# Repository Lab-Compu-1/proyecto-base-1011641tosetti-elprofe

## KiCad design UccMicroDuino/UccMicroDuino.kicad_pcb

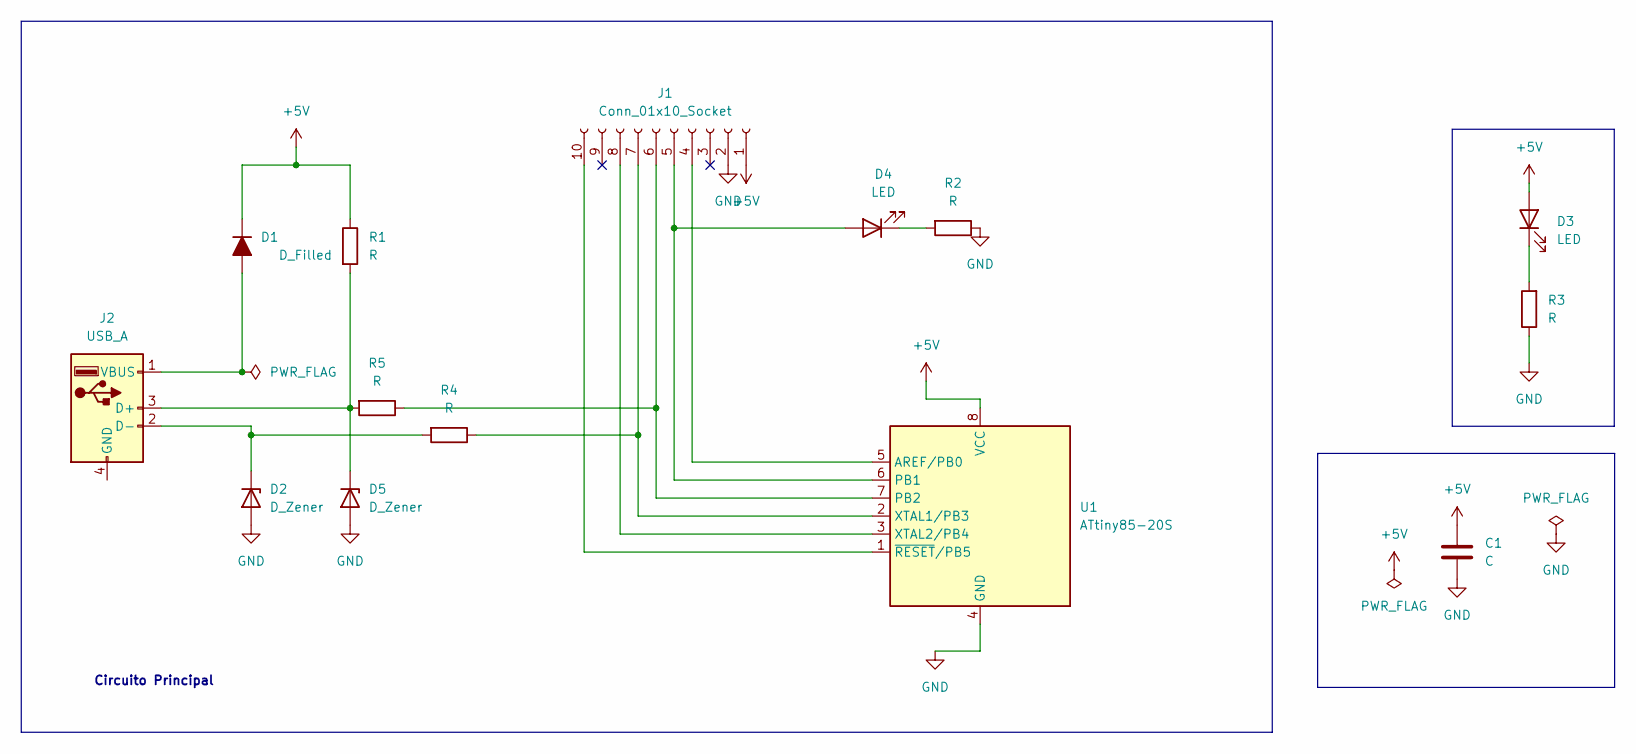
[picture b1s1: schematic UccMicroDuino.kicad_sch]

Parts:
C1: C; C_0805_2012Metric_Pad1.18x1.45mm_HandSolder
D1: D_Filled; D_MiniMELF
D2, D5: D_Zener; D_SOD-123
D3, D4: LED; ledSMD
J1: Conn_01x10_Socket; PinHeader_1x10_P2.54mm_Vertical
J2: USB_A; USB_A_UCC
R1, R2, R3, R4, R5: R; R_0805_2012Metric_Pad1.20x1.40mm_HandSolder
U1: ATtiny85-20S; SOIC-8W_5.3x5.3mm_P1.27mm

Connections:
+5V: C1.1, D1.1 (K), D3.2 (A), J1.1, R1.1, U1.8 (VCC)
GND: C1.2, D2.2 (A), D5.2 (A), J1.2, R2.1, R3.1, U1.4 (GND)
unnamed: D1.2 (A), J2.1 (VBUS)
unnamed: D2.1 (K), J2.2 (D-), R4.2
unnamed: D3.1 (K), R3.2
unnamed: D4.2 (A), J1.5, U1.6 (PB1)
unnamed: D4.1 (K), R2.2
unnamed: D5.1 (K), J2.3 (D+), R1.2, R5.2
unnamed: J1.4, U1.5 (AREF/PB0)
unnamed: J1.6, R5.1, U1.7 (PB2)
unnamed: J1.7, R4.1, U1.2 (XTAL1/PB3)
unnamed: J1.8, U1.3 (XTAL2/PB4)
unnamed: J1.10, U1.1 (~RESET/PB5)

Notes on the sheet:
Circuito Principal

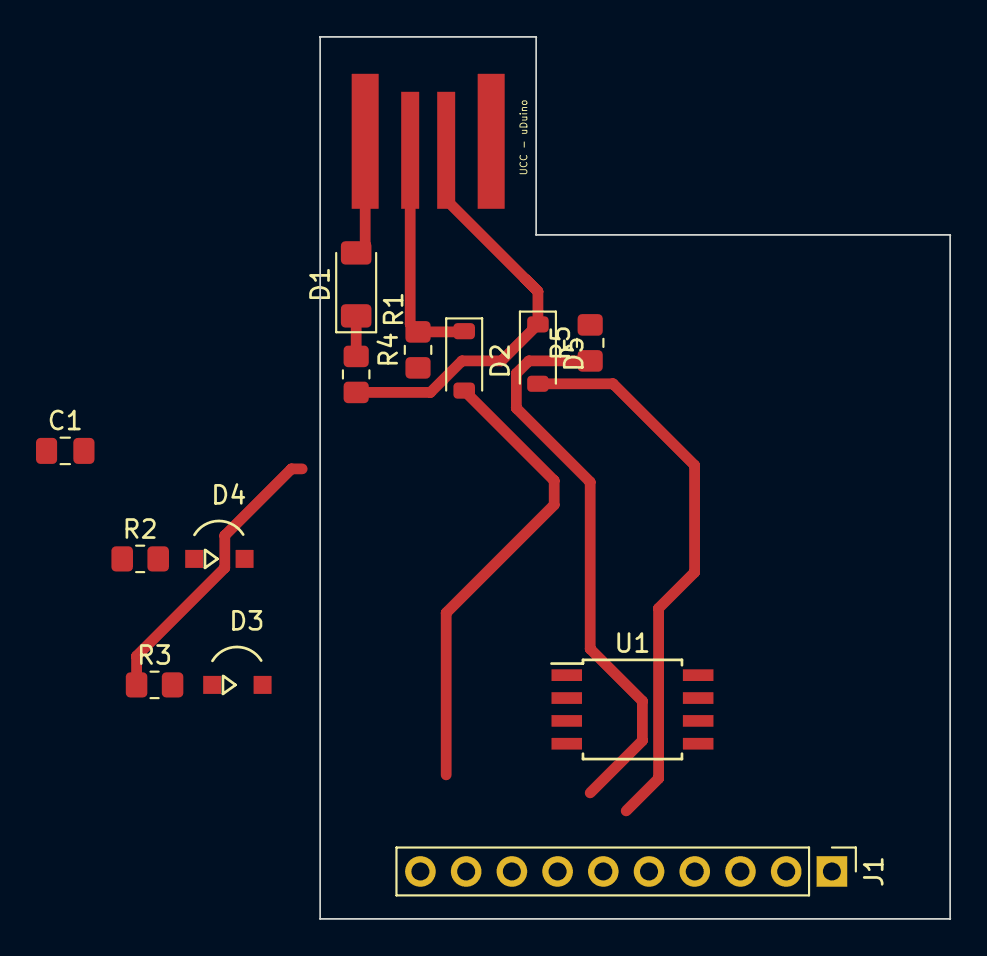
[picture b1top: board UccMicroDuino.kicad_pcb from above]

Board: 2 copper layers, 35.0 x 49.0 mm, 14 parts (0 on the bottom side), 13 nets.

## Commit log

2025-03-17 GitHub Classroom Feedback
2025-03-17 Setting up GitHub Classroom Feedback
2025-04-07 Plano elèctrico en proceso
2025-05-05 Placa prueba didactica
2025-05-12 ruteo basico
2026-05-18 1011641-mi primer versionado con gitBash
2026-05-29 Mi primer commit y entrega de proyecto kicad
2026-05-29 nada
